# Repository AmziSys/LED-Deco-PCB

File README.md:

# LED-Deco-PCB
---------------------------- LED-Deco-PCB -----------------------------

* Intro:
  
  The idea is to design a simple decoration circuit that automatically turns the lights on an off, and it can be used in special events or parties (Astable Multivibrator - Flip Flop)

* Design:

  - LEDs: Red, Green and Orange
  - Transistors
  - Resistors
  - Capacitors
  - Battery (CR-2354/HFN)

* The board was designed using Kicad 8, and simulated on Proteus

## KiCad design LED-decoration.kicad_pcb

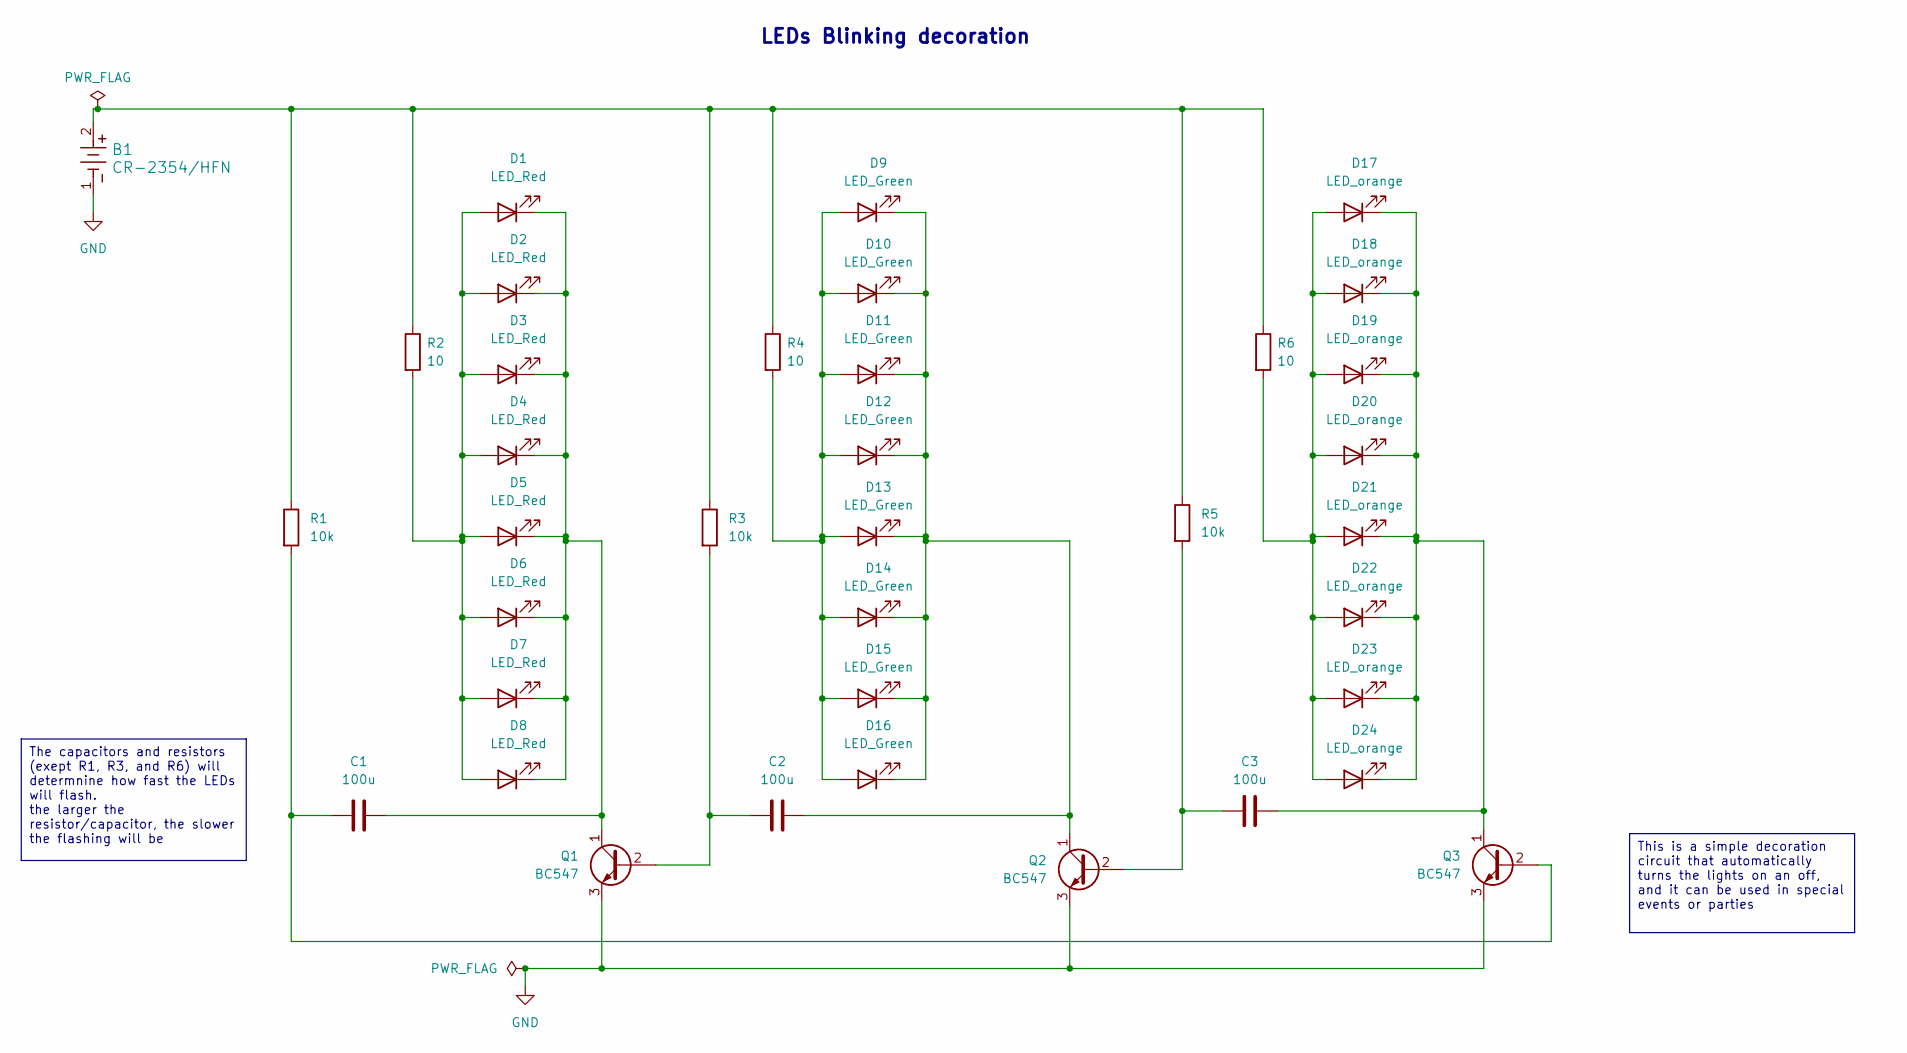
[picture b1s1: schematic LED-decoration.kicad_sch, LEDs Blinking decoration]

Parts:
B1: CR-2354/HFN; BATT_CR-2354-HFN_PAN
C1, C2, C3: 100u; C_1210_3225Metric
D1, D2, D3, D4, D5, D6, D7, D8: LED_Red; LED_D3.0mm
D9, D10, D11, D12, D13, D14, D15, D16: LED_Green; LED_D5.0mm
D17, D18, D19, D20, D21, D22, D23, D24: LED_orange; LED_D5.0mm
Q1, Q2, Q3: BC547; TO-92_Inline
R1, R3, R5: 10k; R_2512_6332Metric
R2, R4, R6: 10; R_1206_3216Metric

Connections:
GND: B1.1, Q1.3 (E), Q2.3 (E), Q3.3 (E)
unnamed: B1.2, R1.1, R2.1, R3.1, R4.1, R5.1, R6.1
unnamed: D1.2 (A), D2.2 (A), D3.2 (A), D4.2 (A), D5.2 (A), D6.2 (A), D7.2 (A), D8.2 (A), R2.2
unnamed: C1.2, D1.1 (K), D2.1 (K), D3.1 (K), D4.1 (K), D5.1 (K), D6.1 (K), D7.1 (K), D8.1 (K), Q1.1 (C)
unnamed: D9.2 (A), D10.2 (A), D11.2 (A), D12.2 (A), D13.2 (A), D14.2 (A), D15.2 (A), D16.2 (A), R4.2
unnamed: C2.2, D9.1 (K), D10.1 (K), D11.1 (K), D12.1 (K), D13.1 (K), D14.1 (K), D15.1 (K), D16.1 (K), Q2.1 (C)
unnamed: D17.2 (A), D18.2 (A), D19.2 (A), D20.2 (A), D21.2 (A), D22.2 (A), D23.2 (A), D24.2 (A), R6.2
unnamed: C3.2, D17.1 (K), D18.1 (K), D19.1 (K), D20.1 (K), D21.1 (K), D22.1 (K), D23.1 (K), D24.1 (K), Q3.1 (C)
unnamed: C2.1, Q1.2 (B), R3.2
unnamed: C3.1, Q2.2 (B), R5.2
unnamed: C1.1, Q3.2 (B), R1.2

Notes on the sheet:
This is a simple decoration circuit that automatically turns the lights on an off, and it can be used in special events or parties
The capacitors and resistors (exept R1, R3, and R6) will determnine how fast the LEDs will flash. the larger the resistor/capacitor, the slower the flashing will be
LEDs Blinking decoration

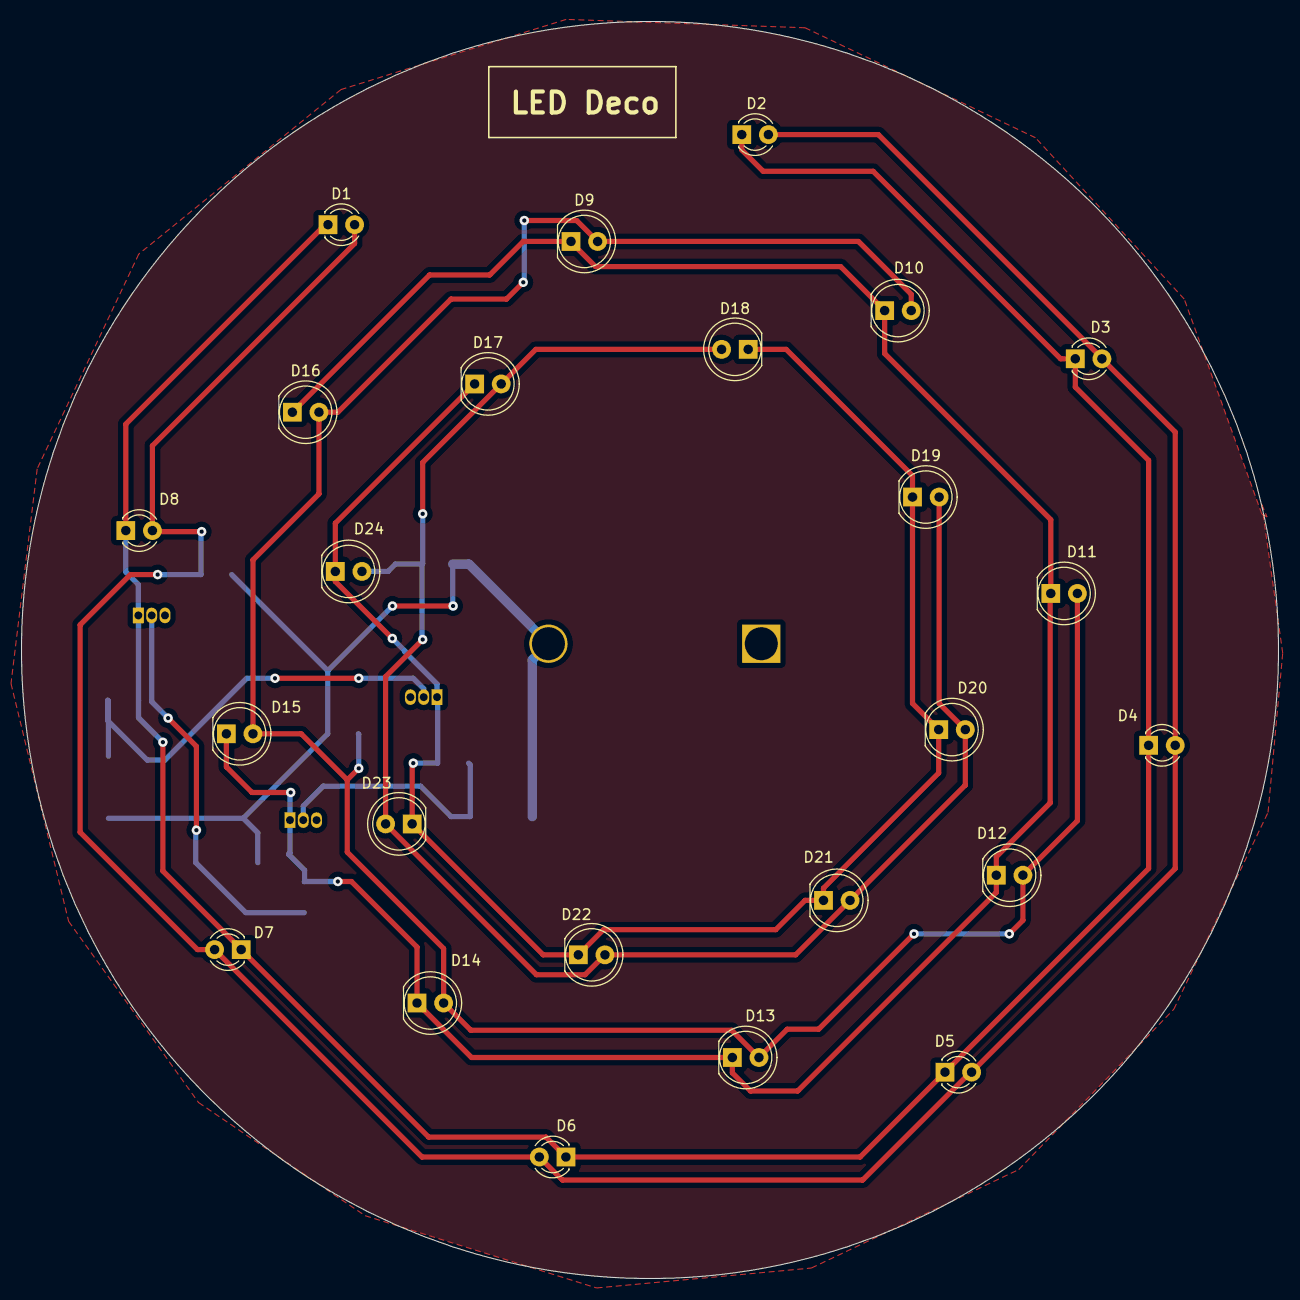
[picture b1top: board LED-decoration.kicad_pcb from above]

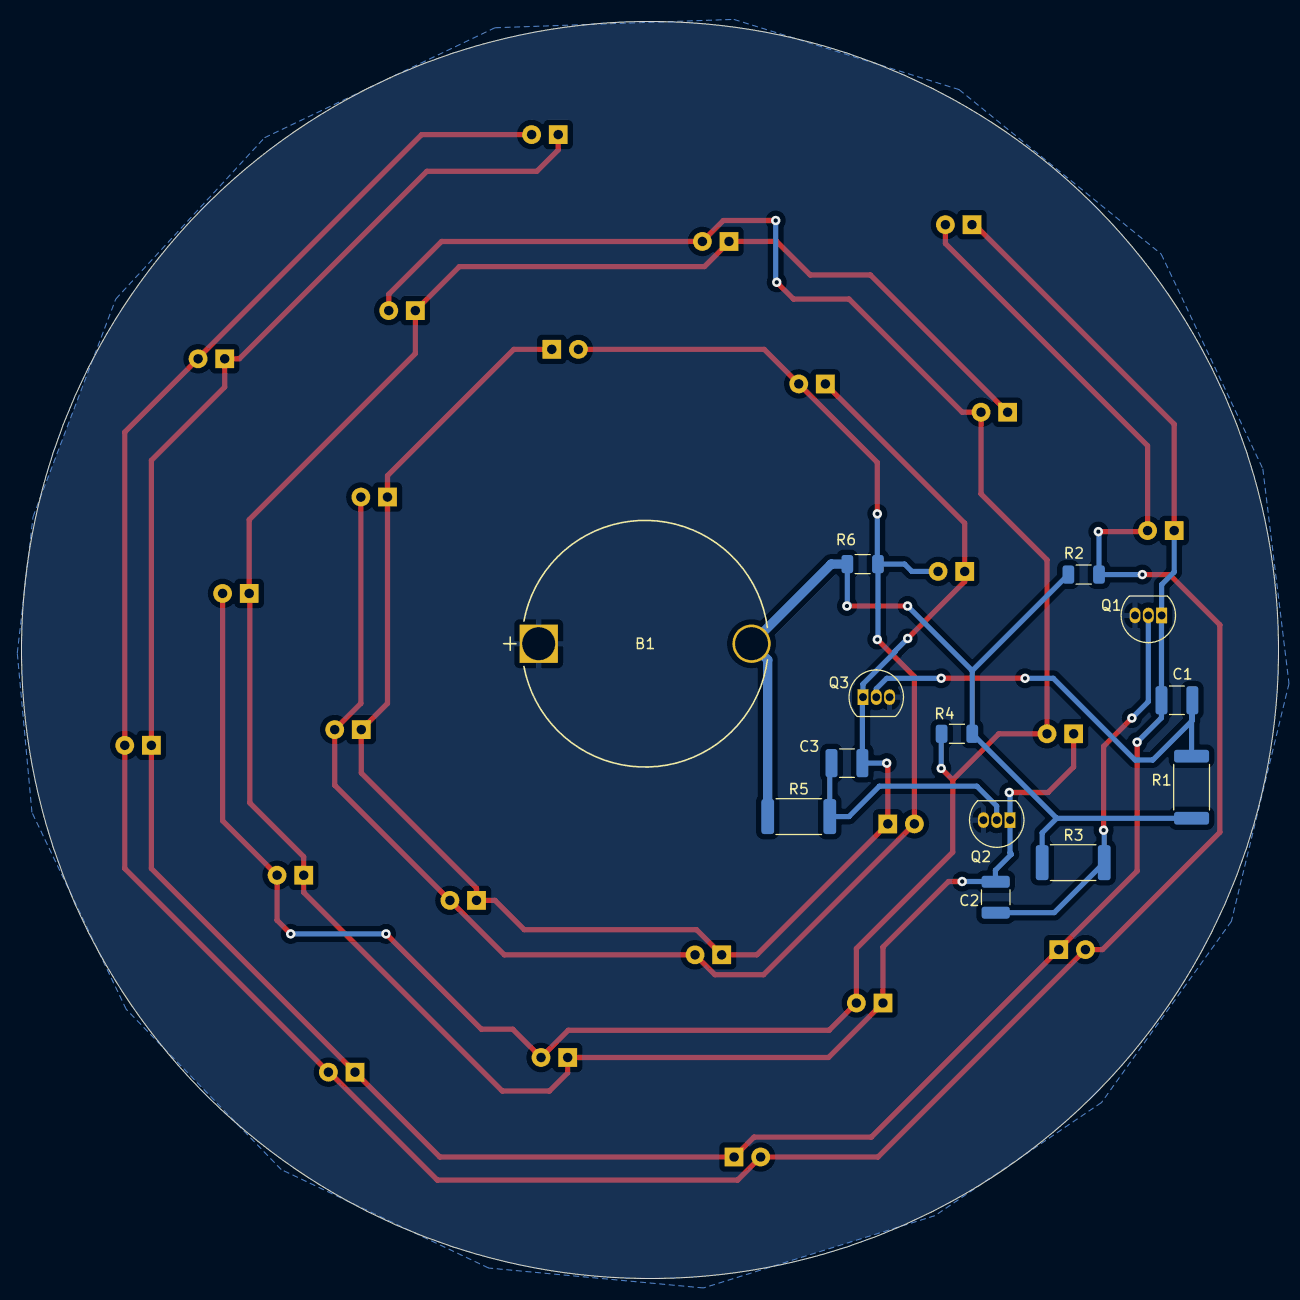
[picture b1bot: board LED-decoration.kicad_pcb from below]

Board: 2 copper layers, 120.0 x 120.0 mm, 37 parts (13 on the bottom side), 11 nets.
